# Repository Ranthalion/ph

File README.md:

View this project on [CADLAB.io](https://cadlab.io/project/2370). 

# ph
pH Module

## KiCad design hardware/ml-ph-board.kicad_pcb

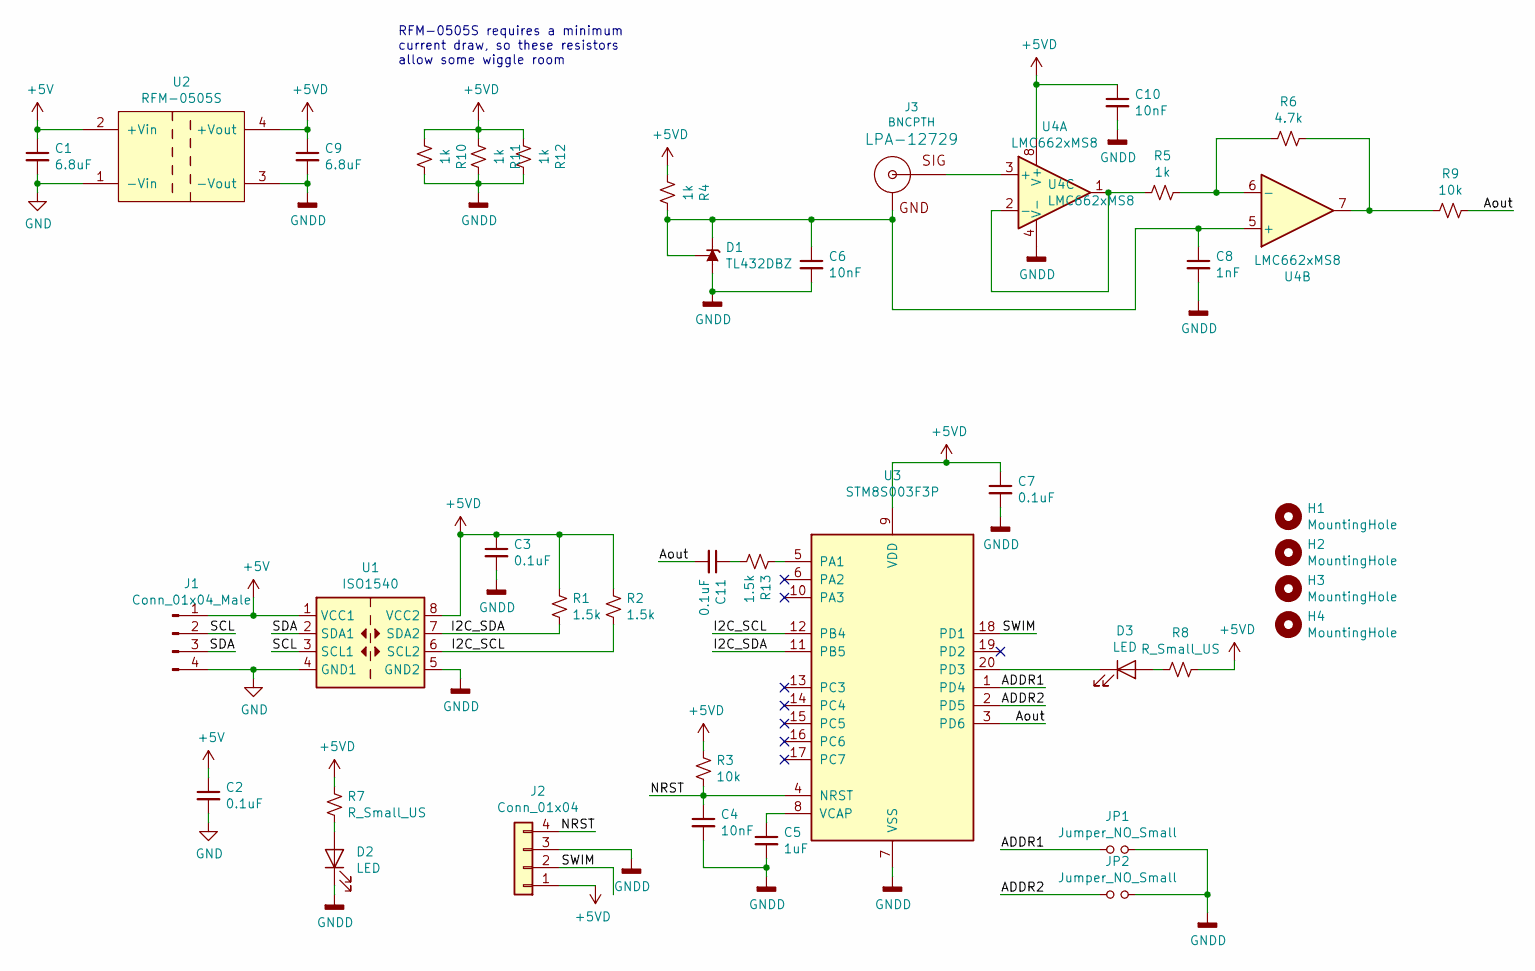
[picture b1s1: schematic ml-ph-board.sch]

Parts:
C1, C9: 6.8uF; C_0603_1608Metric
C2, C3, C7, C11: 0.1uF; C_0603_1608Metric
C4, C6, C10: 10nF; C_0603_1608Metric
C5: 1uF; C_0603_1608Metric
C8: 1nF; C_0603_1608Metric
D1: TL432DBZ; SOT-23
D2, D3: LED; LED_0603_1608Metric_Castellated
H1, H2, H3, H4: MountingHole; MountingHole_3.2mm_M3
J1: Conn_01x04_Male; JST_XH_B04B-XH-A_1x04_P2.50mm_Vertical
J2: Conn_01x04; 1X04_LOCK
J3: BNCPTH; BNC
JP1, JP2: Jumper_NO_Small; SolderJumper-2_P1.3mm_Open_TrianglePad1.0x1.5mm
R1, R2, R13: 1.5k; R_0603_1608Metric
R3, R9: 10k; R_0603_1608Metric
R4, R5, R10, R11, R12: 1k; R_0603_1608Metric
R6: 4.7k; R_0603_1608Metric
R7, R8: R_Small_US; 0603
U1: ISO1540; SOIC-8_3.9x4.9mm_P1.27mm
U2: RFM-0505S; ml_RFM-0505S-SIP4
U3: STM8S003F3P; TSSOP-20_4.4x6.5mm_P0.65mm
U4: LMC662xMS8; SOIC-8_3.9x4.9mm_P1.27mm

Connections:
+5V: C1.1, C2.1, J1.1, U1.1 (VCC1), U2.2 (+Vin)
+5VD: C3.1, C7.1, C9.1, C10.1, J2.1, R1.1, R2.1, R3.1, R4.2, R7.1, R8.1, R10.2, R11.2, R12.2, U1.8 (VCC2), U2.4 (+Vout), U3.9 (VDD), U4.8 (V+)
/ADDR1: JP1.1, U3.1 (PD4)
/ADDR2: JP2.1, U3.2 (PD5)
/Aout: C11.2, R9.1, U3.3 (PD6)
/I2C_SCL: R2.2, U1.6 (SCL2), U3.12 (PB4)
/I2C_SDA: R1.2, U1.7 (SDA2), U3.11 (PB5)
/NRST: C4.1, J2.4, R3.2, U3.4 (NRST)
/SCL: J1.2, U1.3 (SCL1)
/SDA: J1.3, U1.2 (SDA1)
/SWIM: J2.2, U3.18 (PD1)
GND: C1.2, C2.2, J1.4, U1.4 (GND1), U2.1 (-Vin)
GNDD: C3.2, C4.2, C5.2, C6.2, C7.2, C8.2, C9.2, C10.2, D1.3 (A), D2.1 (K), J2.3, JP1.2, JP2.2, R10.1, R11.1, R12.1, U1.5 (GND2), U2.3 (-Vout), U3.7 (VSS), U4.4 (V-)
unnamed: C5.1, U3.8 (VCAP)
unnamed: C6.1, C8.1, D1.1 (REF), D1.2 (K), J3.GND, R4.1, U4.5 (+)
unnamed: C11.1, R13.2
unnamed: D2.2 (A), R7.2
unnamed: D3.1 (K), U3.20 (PD3)
unnamed: D3.2 (A), R8.2
unnamed: J3.S (OUT), U4.3 (+)
unnamed: R5.1, R6.2, U4.6 (-)
unnamed: R5.2, U4.1, U4.2 (-)
unnamed: R6.1, R9.2, U4.7
unnamed: R13.1, U3.5 (PA1)

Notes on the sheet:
RFM-0505S requires a minimum current draw, so these resistors allow some wiggle room

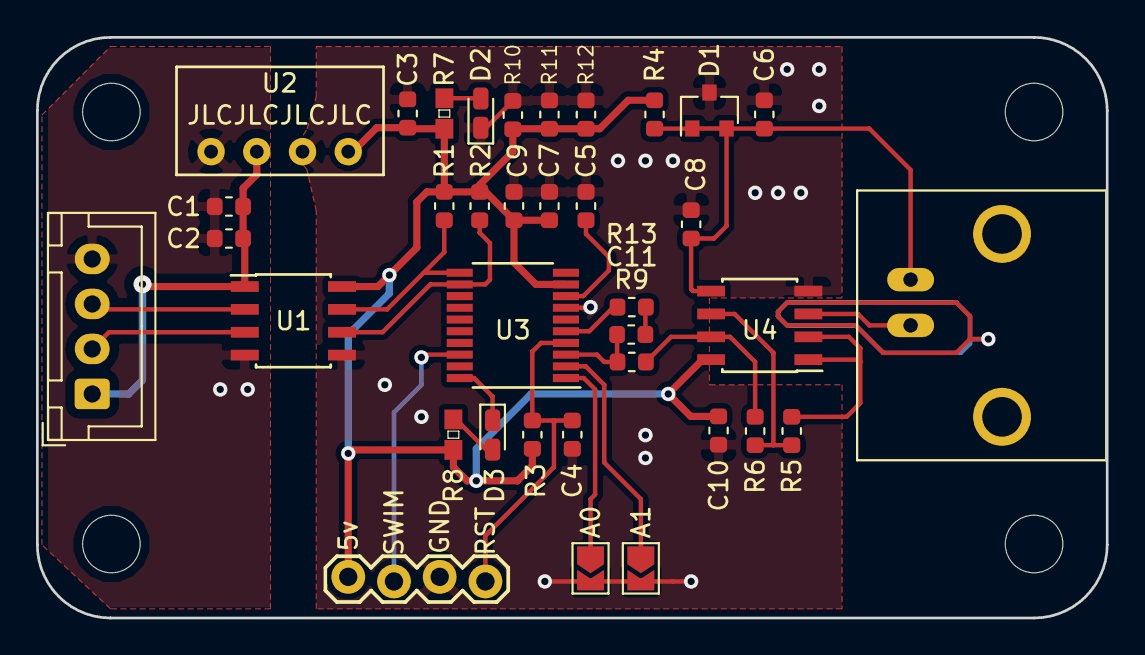
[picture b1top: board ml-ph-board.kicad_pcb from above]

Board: 2 copper layers, 59.4 x 32.3 mm, 40 parts (0 on the bottom side), 24 nets.

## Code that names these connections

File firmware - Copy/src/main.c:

#include "stm8s.h"
#include "main.h"
#include <stdbool.h>
#include "led.h"
#include "stm8s_itc.h"

/*
PA1	ADC
PB4	I2C SCL
PB5	I2C SDA
PD1	SWIM
PD3	LED
PD4	ADDR1
PD5	ADDR2
*/

void init(void);
void clock_setup(void);
void GPIO_setup(void);
void ADC_setup(void);
void I2C_setup(uint16_t address);
void TIM2_setup(void);
void HandleADC(void);
void HandleTimerTick(void);

volatile uint8_t state = 0;
volatile uint16_t phRaw = 1111;

#define BUFFER_SIZE 64
uint16_t adcValues[BUFFER_SIZE];
volatile uint8_t i2cBuffer1[3];
uint8_t idxBuffer = 0;
bool bufferEmpty = true;

uint32_t averagedValue = 0;

volatile uint8_t *startPoint;
volatile uint8_t *currentPoint;

main()
{
	
	
	init();
	i2cBuffer1[0] = 0x03;
	i2cBuffer1[1] = 0x49;
	i2cBuffer1[2] = 0x00;
	//SetLED(LED_OFF, 0);
	//SetLED(LED_PANIC, 1);
	GPIOD->ODR = 0b00011000;
	startPoint = &i2cBuffer1[1];
	currentPoint = startPoint;
	wfi(); //wait for interrupts
	while (1)
	{
		while (state > 0)
		{
			//Check ADC State
			if (state & STATE_ADC_READY)
			{
				HandleADC();				
			}
			
			//Check I2C State
			if (state & STATE_I2C_READY  && 1 == 0)
			{
				state &= ~(STATE_I2C_READY);
			}
			
			//Check TMR State
			if (state & STATE_TMR_TICK)
			{
				LEDTick();
				state &= ~(STATE_TMR_TICK);
			}
		}
		
		wfi();
	}
}

void assert_failed(u8* file, u32 line)
{
	//SetLED(LED_PANIC, 10);
}

void init()
{
	//Clock div / 1
	CLK->CKDIVR = 0;
	
	
	
  //clock_setup();
  //GPIO_setup();
	I2C_setup(0x45);
	
	/* Enable general interrupts */
  enableInterrupts();
	
	ITC_SetSoftwarePriority(ITC_IRQ_TIM2_OVF, ITC_PRIORITYLEVEL_2);
	ITC_SetSoftwarePriority(ITC_IRQ_ADC1, ITC_PRIORITYLEVEL_2);
	
	ADC_setup();
	TIM2_setup();
	
}

void clock_setup(void)
{
  CLK_DeInit();
                                
  CLK_HSECmd(DISABLE);
  CLK_LSICmd(DISABLE);
  CLK_HSICmd(ENABLE);
  while(CLK_GetFlagStatus(CLK_FLAG_HSIRDY) == FALSE);
                                
  CLK_ClockSwitchCmd(ENABLE);
  CLK_HSIPrescalerConfig(CLK_PRESCALER_HSIDIV1);
  CLK_SYSCLKConfig(CLK_PRESCALER_CPUDIV1);
                                
  CLK_ClockSwitchConfig(CLK_SWITCHMODE_AUTO, CLK_SOURCE_HSI, 
		DISABLE, CLK_CURRENTCLOCKSTATE_ENABLE);
                                
  CLK_PeripheralClockConfig(CLK_PERIPHERAL_I2C, ENABLE);
  CLK_PeripheralClockConfig(CLK_PERIPHERAL_SPI, DISABLE);
  CLK_PeripheralClockConfig(CLK_PERIPHERAL_UART1, DISABLE);
  CLK_PeripheralClockConfig(CLK_PERIPHERAL_AWU, DISABLE);
  CLK_PeripheralClockConfig(CLK_PERIPHERAL_ADC, ENABLE);
  CLK_PeripheralClockConfig(CLK_PERIPHERAL_TIMER1, DISABLE);
  CLK_PeripheralClockConfig(CLK_PERIPHERAL_TIMER2, ENABLE);
  CLK_PeripheralClockConfig(CLK_PERIPHERAL_TIMER4, DISABLE);
}

void GPIO_setup()
{
	//Set up LED
  GPIO_DeInit(LED_port);
  GPIO_Init(LED_port, (LED_pin | GPIO_PIN_5), GPIO_MODE_OUT_PP_LOW_FAST);
	//GPIO_Init(LED_port, LED_pin, GPIO_MODE_OUT_PP_LOW_FAST);
	
	//Set up ADDR
	//GPIO_Init(ADDR_port, ADDR_pin_1, GPIO_MODE_IN_PU_NO_IT);
	//GPIO_Init(ADDR_port, ADDR_pin_2, GPIO_MODE_IN_PU_NO_IT);
	
	//Set up  ADC
	GPIO_Init(ADC_port, ADC_pin, GPIO_MODE_IN_FL_NO_IT);
	
	//Set up I2C
	GPIO_Init(GPIOB, GPIO_PIN_4, GPIO_MODE_OUT_OD_HIZ_FAST);
	GPIO_Init(GPIOB, GPIO_PIN_5, GPIO_MODE_OUT_OD_HIZ_FAST);
	
}

void ADC_setup()
{
	ADC1_DeInit();
	
	ADC1_Init(ADC1_CONVERSIONMODE_CONTINUOUS, 
             ADC1_CHANNEL_6,
             ADC1_PRESSEL_FCPU_D12, 
             ADC1_EXTTRIG_GPIO, 
             DISABLE, 
             ADC1_ALIGN_RIGHT, 
             ADC1_SCHMITTTRIG_CHANNEL6, 
             DISABLE);
	ADC1_DataBufferCmd(ENABLE);
	ADC1_ITConfig(ADC1_IT_EOCIE, ENABLE);
	ADC1_Cmd(ENABLE);
}

void I2C_setup(uint16_t address)
{
	I2C_DeInit();
	I2C_Init(100000, 
					 address << 1, 
					 I2C_DUTYCYCLE_2, 
					 I2C_ACK_CURR, 
					 I2C_ADDMODE_7BIT, 
					 (CLK_GetClockFreq() / 1000000));
	//I2C_StretchClockCmd(DISABLE);
	
	/* Enable Error Interrupt*/
  I2C_ITConfig((I2C_IT_TypeDef)(I2C_IT_ERR | I2C_IT_EVT | I2C_IT_BUF), ENABLE);
  
	I2C_Cmd(ENABLE);
}

void TIM2_setup(void)
{
    TIM2_DeInit();
    TIM2_TimeBaseInit(TIM2_PRESCALER_32, 32000);
		TIM2_ITConfig(TIM2_IT_UPDATE, ENABLE);
    TIM2_Cmd(ENABLE);
}

void HandleADC()
{
	uint8_t x = 0;
				
	//Sum the values into the buffer
	adcValues[idxBuffer] = 0;
	for(x = 0; x < 8; x++)
	{
		adcValues[idxBuffer] += (ADC1_GetBufferValue(x) << 3);
	}
	
	//Fill up the buffer with the first value 
	//so averaging isn't skewed toward 0.  
	if(bufferEmpty)
	{
		bufferEmpty = false;
		for(x = 1; x < BUFFER_SIZE; x++)
		{
			adcValues[x] = adcValues[0];
		}
	}
	
	//Average the readings in the buffer
	averagedValue = 0;
	for(x = 0; x < BUFFER_SIZE; x++)
	{
		averagedValue += adcValues[x];
	}
	averagedValue = averagedValue / (BUFFER_SIZE * 8);
	phRaw = averagedValue;
	i2cBuffer1[0] = phRaw >> 8;
	i2cBuffer1[1] = phRaw;
	//Increment buffer and roll over
	idxBuffer++;
	if (idxBuffer >= BUFFER_SIZE)
	{
		idxBuffer = 0;
	}
	
	state &= ~(STATE_ADC_READY);
}

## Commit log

2019-12-14 Add schematic and layout
2019-12-22 Backlink to CADLAB.io has been added.
2019-12-25 firmware
2019-12-25 ADC firmware
2019-12-27 i2c checkpoint
2019-12-28 i2c fixed
2019-12-30 More I2C struggles
2020-01-04 I2C working
2020-01-06 Fix start up issue
2020-01-08 Handle erroneous I2C signals
